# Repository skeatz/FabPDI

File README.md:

## FabPDI
**DIY PDI/ISP programmer**

The thought of building a DIY PDI programmer first came to me during [Embedded Programming](http://archive.fabacademy.org/2016/fablabsingapore/students/98/exercise08.html) week in Fab Academy 2016, when Neil talked about the ATxmega16E5 microcontroller. I was itching to try it out, but lacked a PDI programmer.

After some research, I learned that I could modify a [USBasp](http://www.fischl.de/usbasp/) into a PDI programmer. The second alternative was to build an [AVRISP-MkII clone](http://www.fourwalledcubicle.com/AVRISP.php). Since I had a couple of USBasp boards, I thought "*why not?*"

My attempt at modifying my USBasp board failed and is documented in my Fab Academy [website](http://archive.fabacademy.org/2016/fablabsingapore/students/98/exercise08.html). What I lacked at that time was a [schematic diagram](images/usbasp_v2.0_sch.jpg) of my USBasp board. I soon abandoned the attempt at modifying my USBasp board due to the limited time available, but the desire to build my own PDI programmer stayed with me all the time.

Since Fab Academy 2016, I have managed to build 2 different versions of fabbable PDI programmers, which I have documented here. I have also successfully modified 2 different versions of commercial USBasp boards for PDI programming.

1. [**FabPDI-mega8**](fabpdi-mega8.md)
   * modified USBasp
   * based on ATmega8
   * uses VUSB library
   * both PDI & ISP programmer
2. [**FabPDI-t90usb**](fabpdi-t90usb.md)
   * AVRISP-MkII compatible
   * based on AT90usb162
   * uses LUFA library
   * both PDI & ISP programmer
3. [**USBasp PDI programmer**](usbasp-mods.md)
   * modified commercial USBasp boards
   * both PDI & ISP programmer

My collection of DIY and modified PDI programmer boards:

*PDI boards collection (from left): FabPDI-mega8, FabPDI-t90usb, USBasp v2.0 (LC Technology), USBasp (Baite)*

*Copyright (c) 2017 Steven Chew*

*MIT license*

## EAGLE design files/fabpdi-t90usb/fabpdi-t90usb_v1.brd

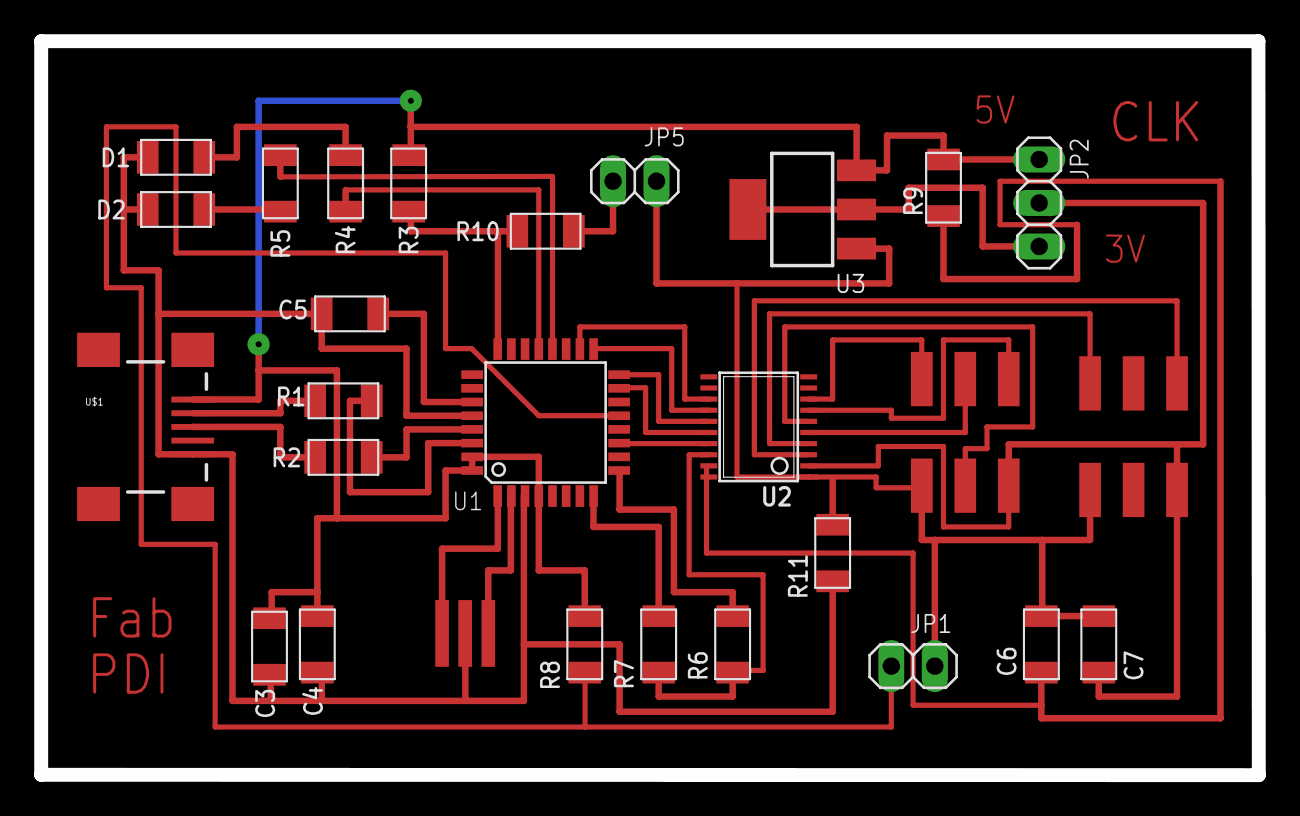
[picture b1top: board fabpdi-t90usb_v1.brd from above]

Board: 2 copper layers, 71.1 x 42.9 mm, 28 parts (0 on the bottom side), 34 nets.

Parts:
C3, C6, C7: 0.1u; C1206FAB
C4: 10u; C1206FAB
C5: 1u; C1206FAB
D1: red; LED1206FAB
D2: green; LED1206FAB
JP1, JP5: 1X02
JP2: 1X03
JP3: ISP; 2X03SMD-FAB
JP4: PDI; 2X03SMD-FAB
R1, R2, R6, R7: 49; R1206FAB
R3: 10k; R1206FAB
R4, R5, R8: 1k; R1206FAB
R9: 100k; R1206FAB
R10, R11: 0; R1206FAB
U1: AT90USB162A; TQFP32-08
U2: GTL2003PW; TSSOP20
U3: AMS1117-3.3; SOT-223
U$1: USB_MINI
X1: 16MHz; EFOBM

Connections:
GND: C3.1, C4.1, C5.1, D1.2, D2.2, U1.3, U1.28, U$1.GND, X1.2
unnamed: R4.1, U1.21
unnamed: C5.2, U1.27
unnamed: U1.1, X1.1
unnamed: U1.2, X1.3
unnamed: R2.1, U$1.D+
unnamed: R2.2, U1.29
unnamed: R1.1, U$1.D-
unnamed: R1.2, U1.30
unnamed: R3.1, R10.2, U1.24
unnamed: R5.1, U1.20
unnamed: D1.1, R4.2
unnamed: D2.1, R5.2
unnamed: U1.11, U2.17
unnamed: R6.1, U1.9
unnamed: R7.1, U1.8
unnamed: JP1.2, R8.1, U1.13
unnamed: R6.2, R7.2, U2.18
unnamed: U1.15, U2.16
unnamed: U1.16, U2.15
unnamed: U1.17, U2.14
unnamed: U1.18, U2.13
unnamed: C6.2, R9.1, U2.20
unnamed: JP3.1, U2.7
unnamed: JP2.3, U3.2, U3.TER
unnamed: JP3.3, U2.5
unnamed: JP3.4, U2.6
unnamed: JP3.5, U2.8
unnamed: JP4.5, U2.4
unnamed: JP4.1, U2.3
unnamed: JP5.1, R10.1
S$1: C6.1, C7.1, JP1.1, JP3.6, JP4.6, JP5.2, U2.1, U3.1
V+: C7.2, JP2.2, JP3.2, JP4.2, U2.2
VCC: C3.2, C4.2, JP2.1, R3.2, R8.2, R9.2, U1.4, U1.31, U1.32, U3.3, U$1.VBUS

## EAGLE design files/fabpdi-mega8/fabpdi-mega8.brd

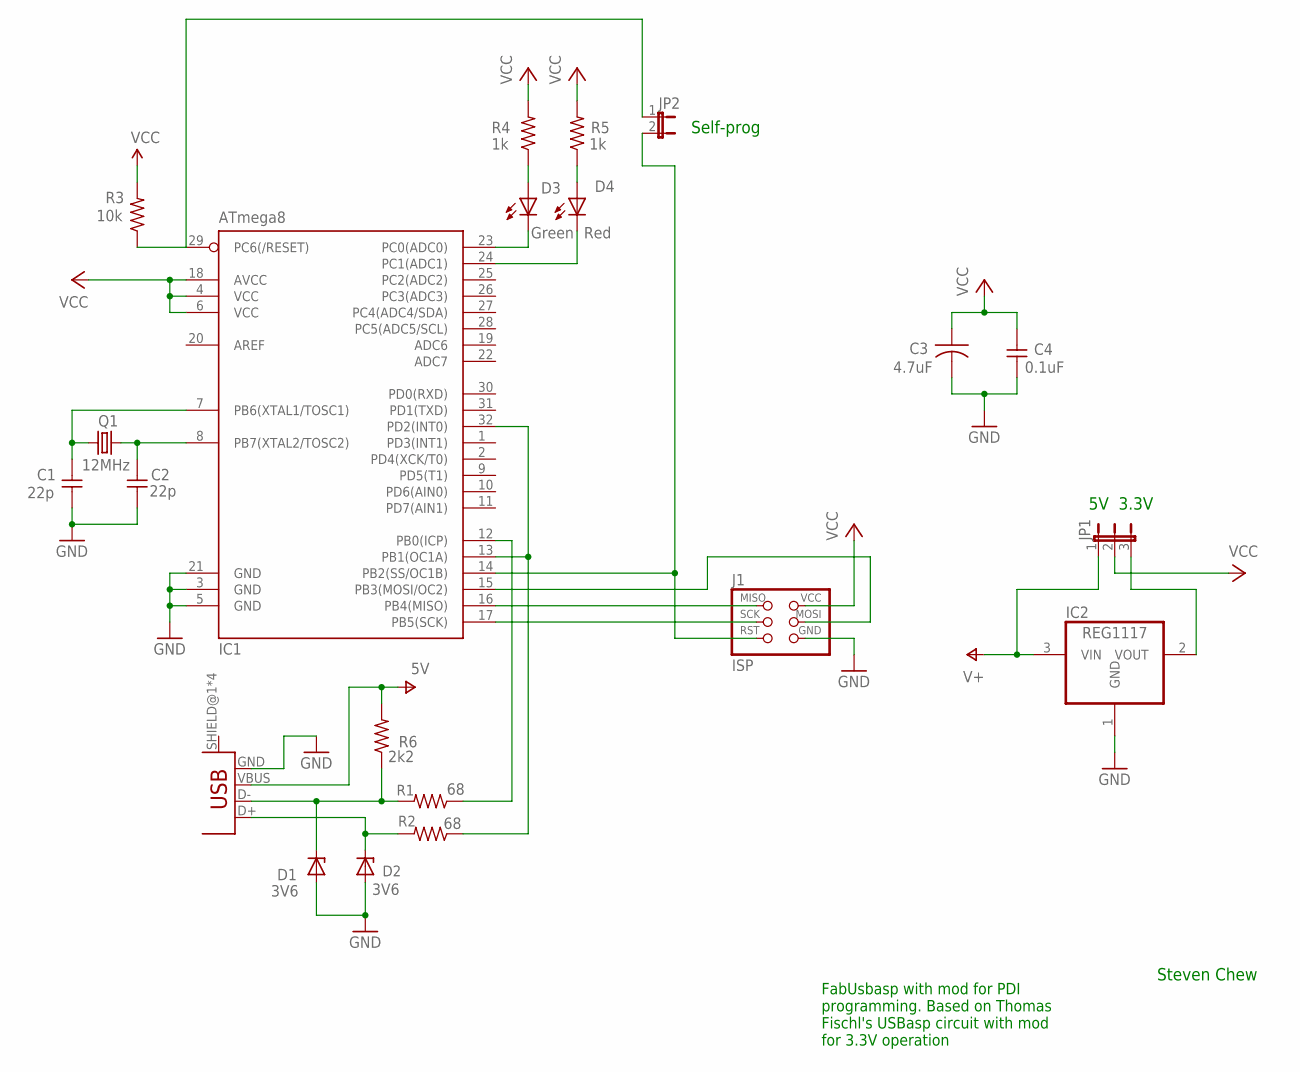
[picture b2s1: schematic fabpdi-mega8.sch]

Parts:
C1, C2: 22p; C1206FAB
C3: 4.7uF; C1206FAB
C4: 0.1uF; C1206FAB
D1, D2: 3V6; SOD123
D3: Green; LED1206FAB
D4: Red; LED1206FAB
IC1: ATmega8; TQFP32-08THIN
IC2: REG1117; SOT223
J1: ISP; 2X03SMD
JP1: JP2E; JP2
JP2: JP1E; JP1
Q1: 12MHz; 2-SMD-5X3MM
R1, R2: 68; R1206FAB
R3: 10k; R1206FAB
R4, R5: 1k; R1206FAB
R6: 2k2; R1206FAB
U$1: USB_MINIB

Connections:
GND: C1.1, C2.1, C3.2, C4.1, D1.ANODE, D2.ANODE, IC1.3 (GND), IC1.5 (GND), IC1.21 (GND), IC2.1 (GND), J1.6 (GND), U$1.GND
unnamed: C2.2, IC1.8 (PB7(XTAL2/TOSC2)), Q1.P$2 (2)
unnamed: C1.2, IC1.7 (PB6(XTAL1/TOSC1)), Q1.P$1 (1)
unnamed: IC1.12 (PB0(ICP)), R1.1
unnamed: D1.CATHODE, R1.2, R6.1, U$1.D-
unnamed: D2.CATHODE, R2.2, U$1.D+
unnamed: D3.2 (C), IC1.23 (PC0(ADC0))
unnamed: IC1.16 (PB4(MISO)), J1.1 (MISO)
unnamed: IC1.17 (PB5(SCK)), J1.3 (SCK)
unnamed: IC1.15 (PB3(MOSI/OC2)), J1.4 (MOSI)
unnamed: IC1.29 (PC6(/RESET)), JP2.1, R3.1
unnamed: D3.1 (A), R4.1
unnamed: D4.2 (C), IC1.24 (PC1(ADC1))
unnamed: D4.1 (A), R5.1
unnamed: IC1.14 (PB2(SS/OC1B)), J1.5 (RST), JP2.2
unnamed: IC1.13 (PB1(OC1A)), IC1.32 (PD2(INT0)), R2.1
unnamed: IC2.2 (VOUT), JP1.3
V+: IC2.3 (VIN), JP1.1, R6.2, U$1.VBUS
VCC: C3.1, C4.2, IC1.4 (VCC), IC1.6 (VCC), IC1.18 (AVCC), J1.2 (VCC), JP1.2, R3.2, R4.2, R5.2

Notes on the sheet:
FabUsbasp with mod for PDI programming. Based on Thomas Fischl's USBasp circuit with mod for 3.3V operation
Steven Chew
Self-prog
5V 3.3V

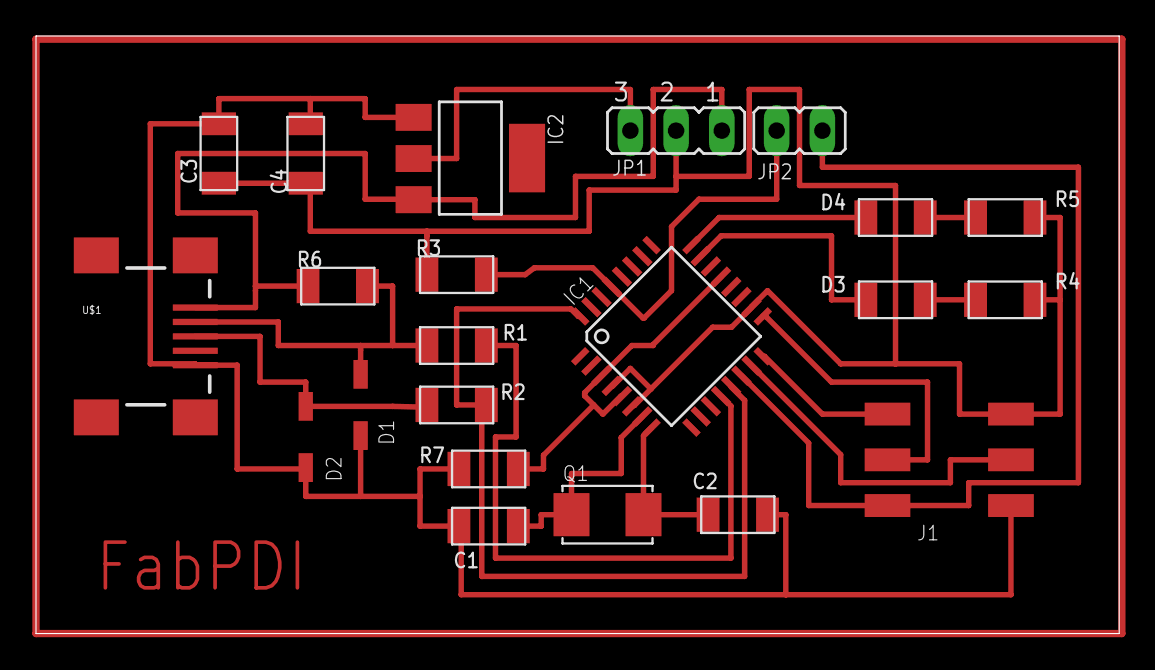
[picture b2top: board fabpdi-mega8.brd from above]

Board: 2 copper layers, 60.2 x 33.2 mm, 22 parts (0 on the bottom side), 19 nets.

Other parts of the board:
R7: 0; R1206FAB

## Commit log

2017-07-15 added eagle files
2017-07-16 updated READ.MD
2017-07-16 labelled boards collection
2017-07-16 Added FabPDI-mega8 files
2017-07-16 Updated fabpdi-mega8 files
2017-07-16 added components list
2017-07-16 updated mega8 md file
2017-07-16 updated t90 design files
2017-07-16 added fabpdi-t90 files
2017-07-23 Updated pix resolutions, fabpdi-t90usb.md
2017-07-23 Uploaded t90-pdi tutorial
2017-07-23 Corrected typos in fabpdi-t90usb.md
2017-07-25 Uploaded usbasp-mods.md
2018-01-23 Set theme jekyll-theme-cayman

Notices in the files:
parts and their libraries:
SparkFun-Aesthetics: Licensing: Creative Commons ShareAlike 4.0 International - https://creativecommons.org/licenses/by-sa/4.0
